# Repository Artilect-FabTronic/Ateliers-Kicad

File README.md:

# Ateliers-Kicad
projets atour de Kicad

premier projet autour de l'arduino UNO, avec l'aide de exploreembedded.com

http://exploreembedded.com/wiki/KiCAD:_Advanced_Tutorials:Arduino_UNO_with_KiCAD

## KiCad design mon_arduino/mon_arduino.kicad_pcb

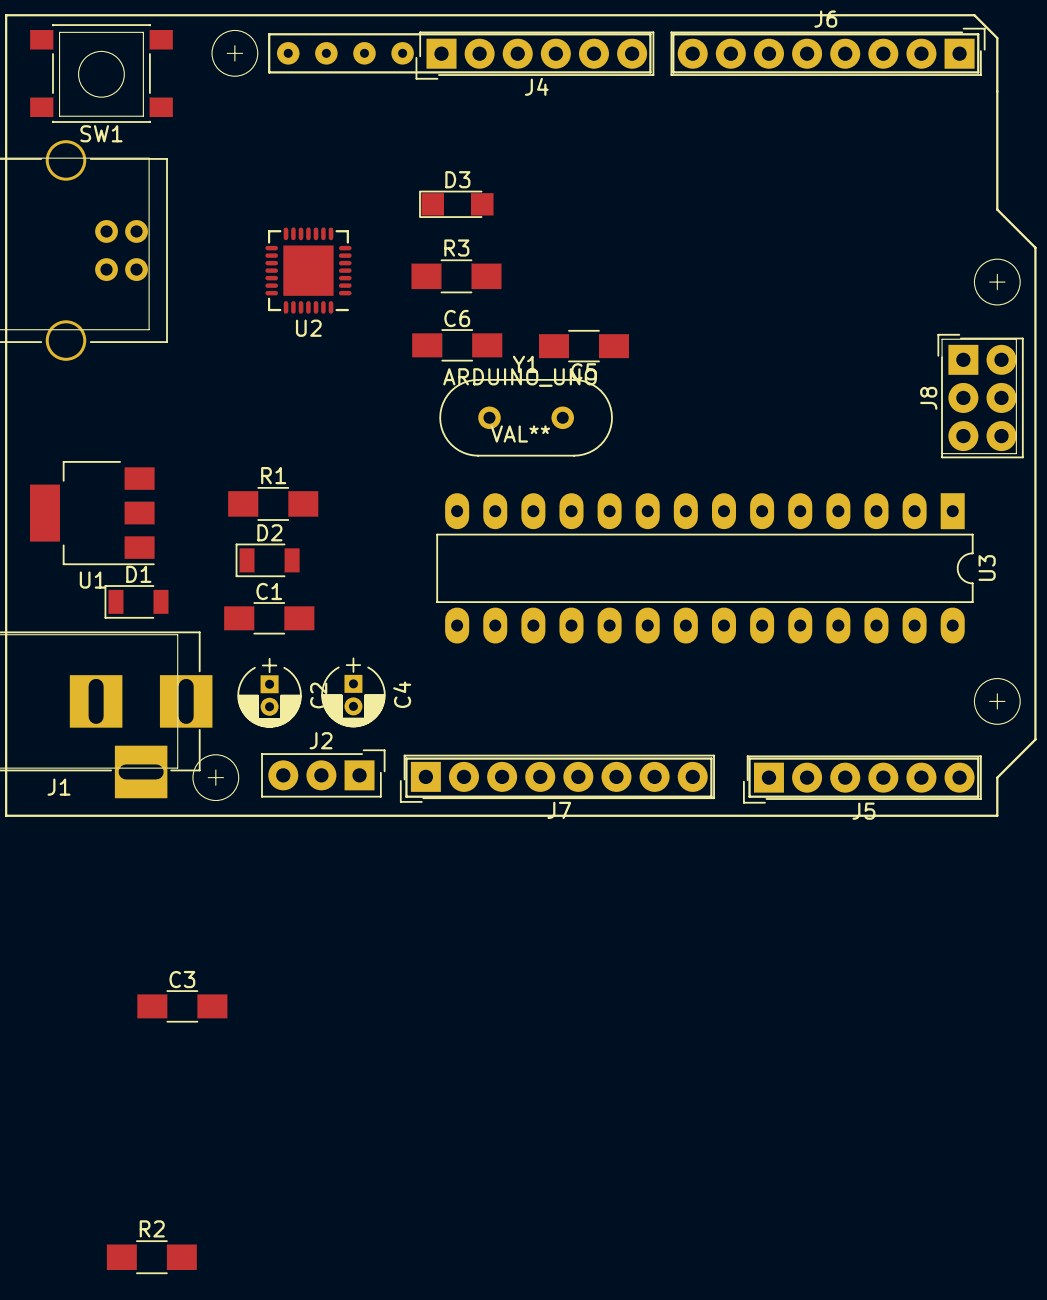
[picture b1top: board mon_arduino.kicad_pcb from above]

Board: 2 copper layers, 26 parts (0 on the bottom side), 36 nets, no tracks yet.

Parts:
ARDUINO_UNO: VAL**; ARDUINO_as_UNO_R3_CONTOUR
C1: 100uF; C_1206_HandSoldering
C2: 100uF/25V; CP_Radial_D4.0mm_P1.50mm
C3: 0.1uF; C_1206_HandSoldering
C4: 10uF; CP_Radial_D4.0mm_P1.50mm
C5, C6: C; C_1206_HandSoldering
D1, D2: D; D_1206
D3: LED; LED_1206
J1: Barrel_Jack; BARREL_JACK
J2: pwr; SL-103-X-XX_1x03
J3: USB_B
J4: Digital IO; SL-106-X-XX_1x06
J5: Analog In; SL-106-X-XX_1x06
J6: Digital IO; SL-108-X-XX_1x08
J7: PWR; SL-108-X-XX_1x08
J8: ICSP; SDL-106-X-XX_2x03
R1: 470; R_1206_HandSoldering
R2, R3: R; R_1206_HandSoldering
SW1: SW_SPST; SW_SPST_PTS645
U1: LM7805_TO220; SOT-223-3_TabPin2
U2: CP2102; QFN-28-1EP_5x5mm_Pitch0.5mm
U3: ATMEGA8A-PU; DIP-28_W7.62mm_LongPads
Y1: 16MHz; Crystal_HC49-4H_Vertical

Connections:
/3.3V: J7.4, U2.6
/5V: J2.3, J7.5, U1.3
/RST: J7.3, J8.5, R2.2, SW1.1, U2.28, U3.1
/RXD: J6.1, U2.26, U3.2
/TXD: J6.2, U2.25, U3.3
/USB_5V: J2.1, J3.1, U2.8
/VIN: D1.2, J1.1, J7.8
GND: C1.2, C2.1, C5.2, C6.2, D2.1, D3.1, J1.2, J1.3, J3.4, J7.6, J7.7, J8.6, SW1.2, U1.2, U2.3, U3.8, U3.22
unnamed: C1.1, C2.2, D1.1, U1.1
unnamed: C3.1, C4.1
unnamed: C3.2, C4.2
unnamed: C5.1, U3.9, Y1.2
unnamed: C6.1, U3.10, Y1.1
unnamed: D2.2, R1.2
unnamed: D3.2, R3.1
unnamed: J3.2, U2.5
unnamed: J3.3, U2.4
unnamed: J4.1, U3.14
unnamed: J4.2, U3.15
unnamed: J4.3, U3.16
unnamed: J4.4, J8.4, U3.17
unnamed: J4.5, J8.1, U3.18
unnamed: J4.6, J8.3, R3.2, U3.19
unnamed: J5.1, U3.23
unnamed: J5.2, U3.24
unnamed: J5.3, U3.25
unnamed: J5.4, U3.26
unnamed: J5.5, U3.27
unnamed: J5.6, U3.28
unnamed: J6.3, U3.4
unnamed: J6.4, U3.5
unnamed: J6.5, U3.6
unnamed: J6.6, U3.11
unnamed: J6.7, U3.12
unnamed: J6.8, U3.13
VCC: J2.2, J8.2, R1.1, U3.7, U3.20, U3.21

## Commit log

2018-02-28 fichiers kicad
